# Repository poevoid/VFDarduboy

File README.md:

# VFDarduboy
interfacing a vfd for arduboy using teensy 4.0

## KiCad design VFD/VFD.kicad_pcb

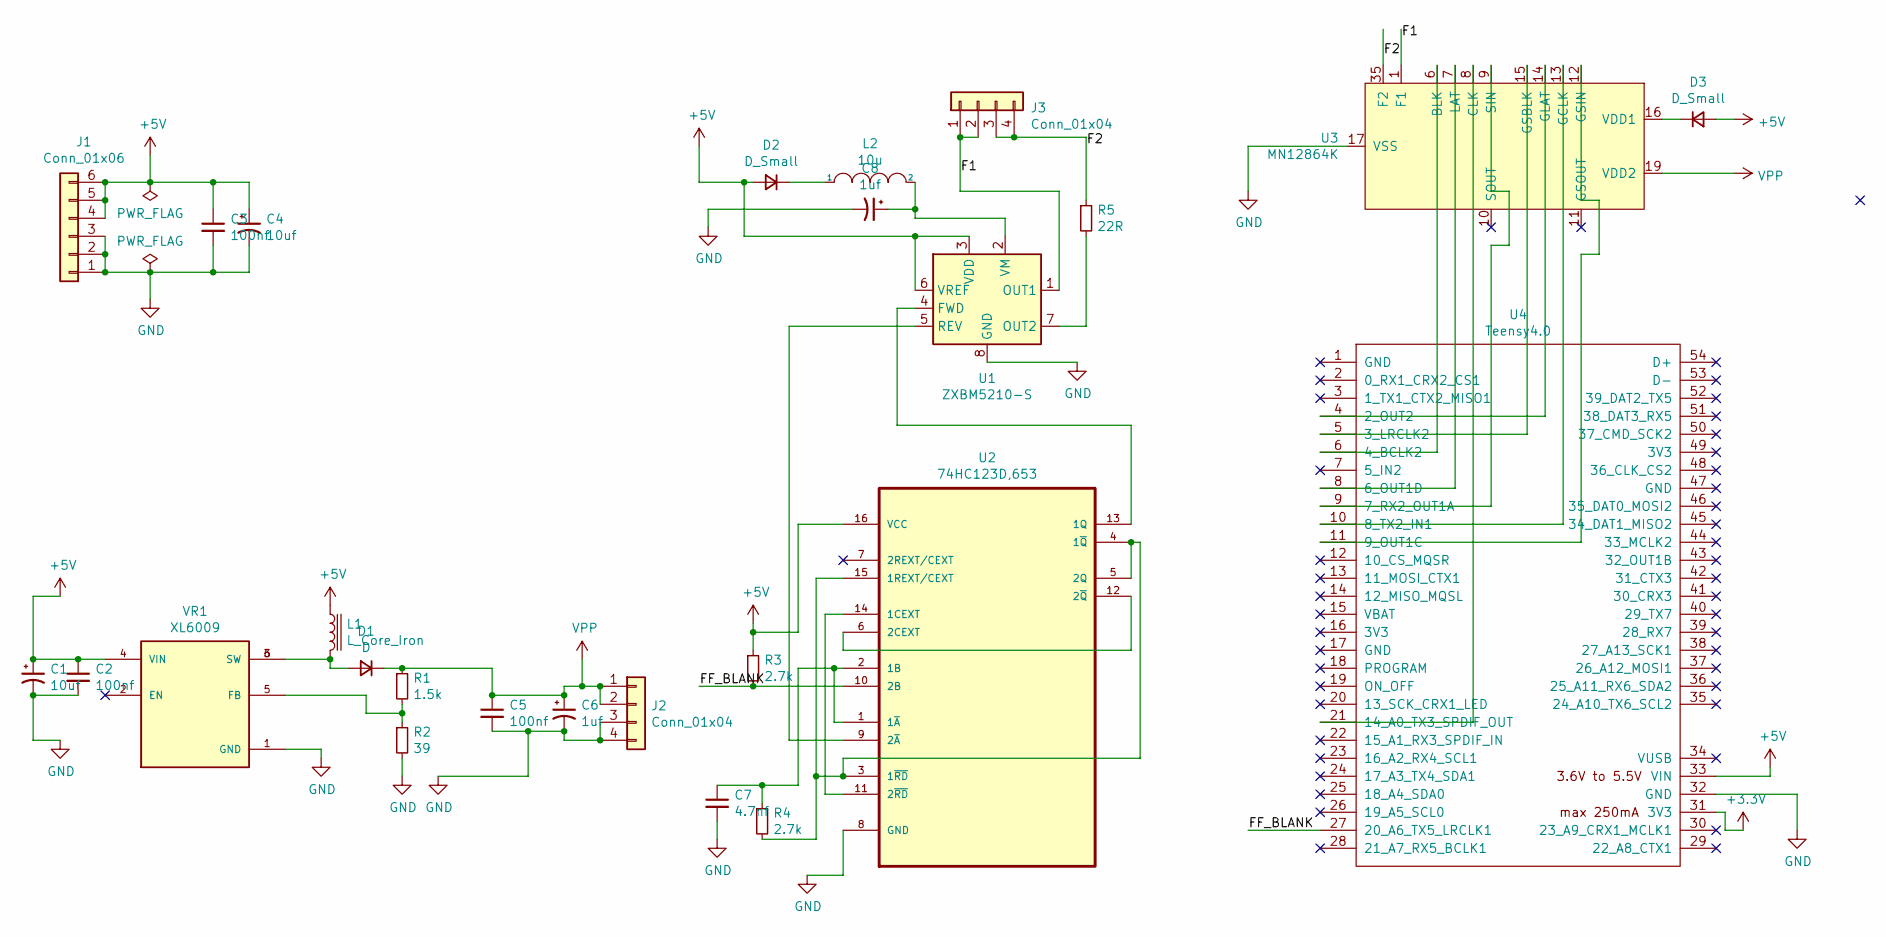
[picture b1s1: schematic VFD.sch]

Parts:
C1, C4: 10uf; CP_Elec_3x5.3
C2, C3, C5: 100nf; C_0201_0603Metric
C6, C8: 1uf; CP_Elec_3x5.3
C7: 4.7nf; C_0201_0603Metric
D1: D; D_0201_0603Metric
D2: D_Small; D_0402_1005Metric
D3: D_Small; D_0201_0603Metric
J1: Conn_01x06; JST_EH_B6B-EH-A_1x06_P2.50mm_Vertical
J2, J3: Conn_01x04; JST_EH_B4B-EH-A_1x04_P2.50mm_Vertical
L1: L_Core_Iron; INDM1250X1250X600
L2: 10u; L_12x12mm_H8mm
R1: 1.5k; R_0201_0603Metric
R2: 39; R_0201_0603Metric
R3, R4: 2.7k; R_0201_0603Metric
R5: 22R; R_0201_0603Metric
U1: ZXBM5210-S; SOIC-8_3.9x4.9mm_P1.27mm
U2: 74HC123D,653; SOIC127P600X175-16N; MPN 74HC123D,653
U3: MN12864K
U4: Teensy4.0; Teensy40
VR1: XL6009; DPAK170P1435X465-6N; PARTREV 1.1

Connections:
+3V3: U4.31 (3V3)
+5V: C1.1, C2.1, C3.1, C4.1, D2.2 (A), D3.2 (A), J1.4, J1.5, J1.6, L1.1, R3.1, U1.3 (VDD), U1.6 (VREF), U2.16 (VCC), U4.33 (VIN), VR1.4 (VIN)
/F1: J3.1, J3.2, U1.1 (OUT1), U3.1 (F1), U3.2 (F1), U3.3 (F1)
/F2: J3.3, J3.4, R5.1, U3.35 (F2), U3.36 (F1), U3.37 (F1)
/FF_BLANK: R3.2, U2.10 (2B), U4.27 (20_A6_TX5_LRCLK1)
GND: C1.2, C2.2, C3.2, C4.2, C5.2, C6.2, C7.2, C8.2, J1.1, J1.2, J1.3, J2.3, J2.4, R2.2, U1.8 (GND), U2.8 (GND), U3.17 (VSS), U3.18 (VSS), U4.32 (GND), VR1.1 (GND)
unnamed: C7.1, R4.1, U2.1 (1~A), U2.2 (1B)
unnamed: C8.1, L2.2, U1.2 (VM)
unnamed: D1.2 (A), L1.2, VR1.3 (SW), VR1.6 (SW)
unnamed: D2.1 (K), L2.1
unnamed: D3.1 (K), U3.16 (VDD1)
unnamed: R1.2, R2.1, VR1.5 (FB)
unnamed: R4.2, U2.3 (1~RD), U2.4 (1~Q), U2.5 (2Q), U2.15 (1REXT/CEXT)
unnamed: R5.2, U1.7 (OUT2)
unnamed: U1.4 (FWD), U2.13 (1Q)
unnamed: U1.5 (REV), U2.9 (2~A)
unnamed: U2.11 (2~RD), U2.14 (1CEXT)
unnamed: U2.6 (2CEXT), U2.12 (2~Q)
unnamed: U3.6 (BLK), U4.6 (4_BCLK2)
unnamed: U3.7 (LAT), U4.8 (6_OUT1D)
unnamed: U3.8 (CLK), U4.21 (14_A0_TX3_SPDIF_OUT)
unnamed: U3.9 (SIN), U4.9 (7_RX2_OUT1A)
unnamed: U3.12 (GSIN), U4.11 (9_OUT1C)
unnamed: U3.13 (GCLK), U4.10 (8_TX2_IN1)
unnamed: U3.14 (GLAT), U4.4 (2_OUT2)
unnamed: U3.15 (GSBLK), U4.5 (3_LRCLK2)
VDD2: C5.1, C6.1, D1.1 (K), J2.1, J2.2, R1.1, U3.19 (VDD2), U3.20 (VDD2)

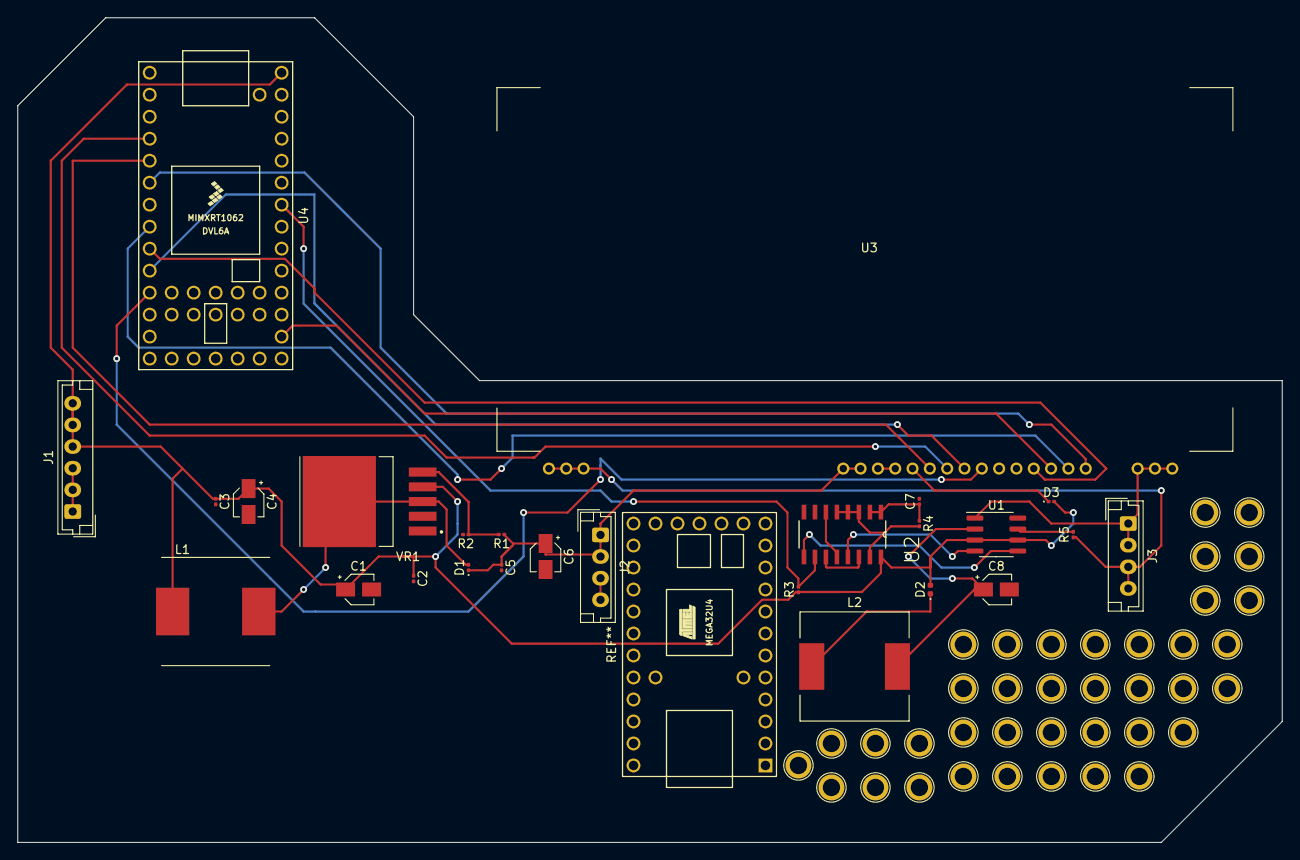
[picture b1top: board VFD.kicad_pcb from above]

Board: 2 copper layers, 146.0 x 95.2 mm, 26 parts (0 on the bottom side), 26 nets.

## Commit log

2021-10-05 Kicad and gerber files
